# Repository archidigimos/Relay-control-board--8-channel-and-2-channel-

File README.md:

# Relay-control-board--8-channel-and-2-channel-
8 and 2 channel Relay control board. Both SMD and Throughole component version have been developed.

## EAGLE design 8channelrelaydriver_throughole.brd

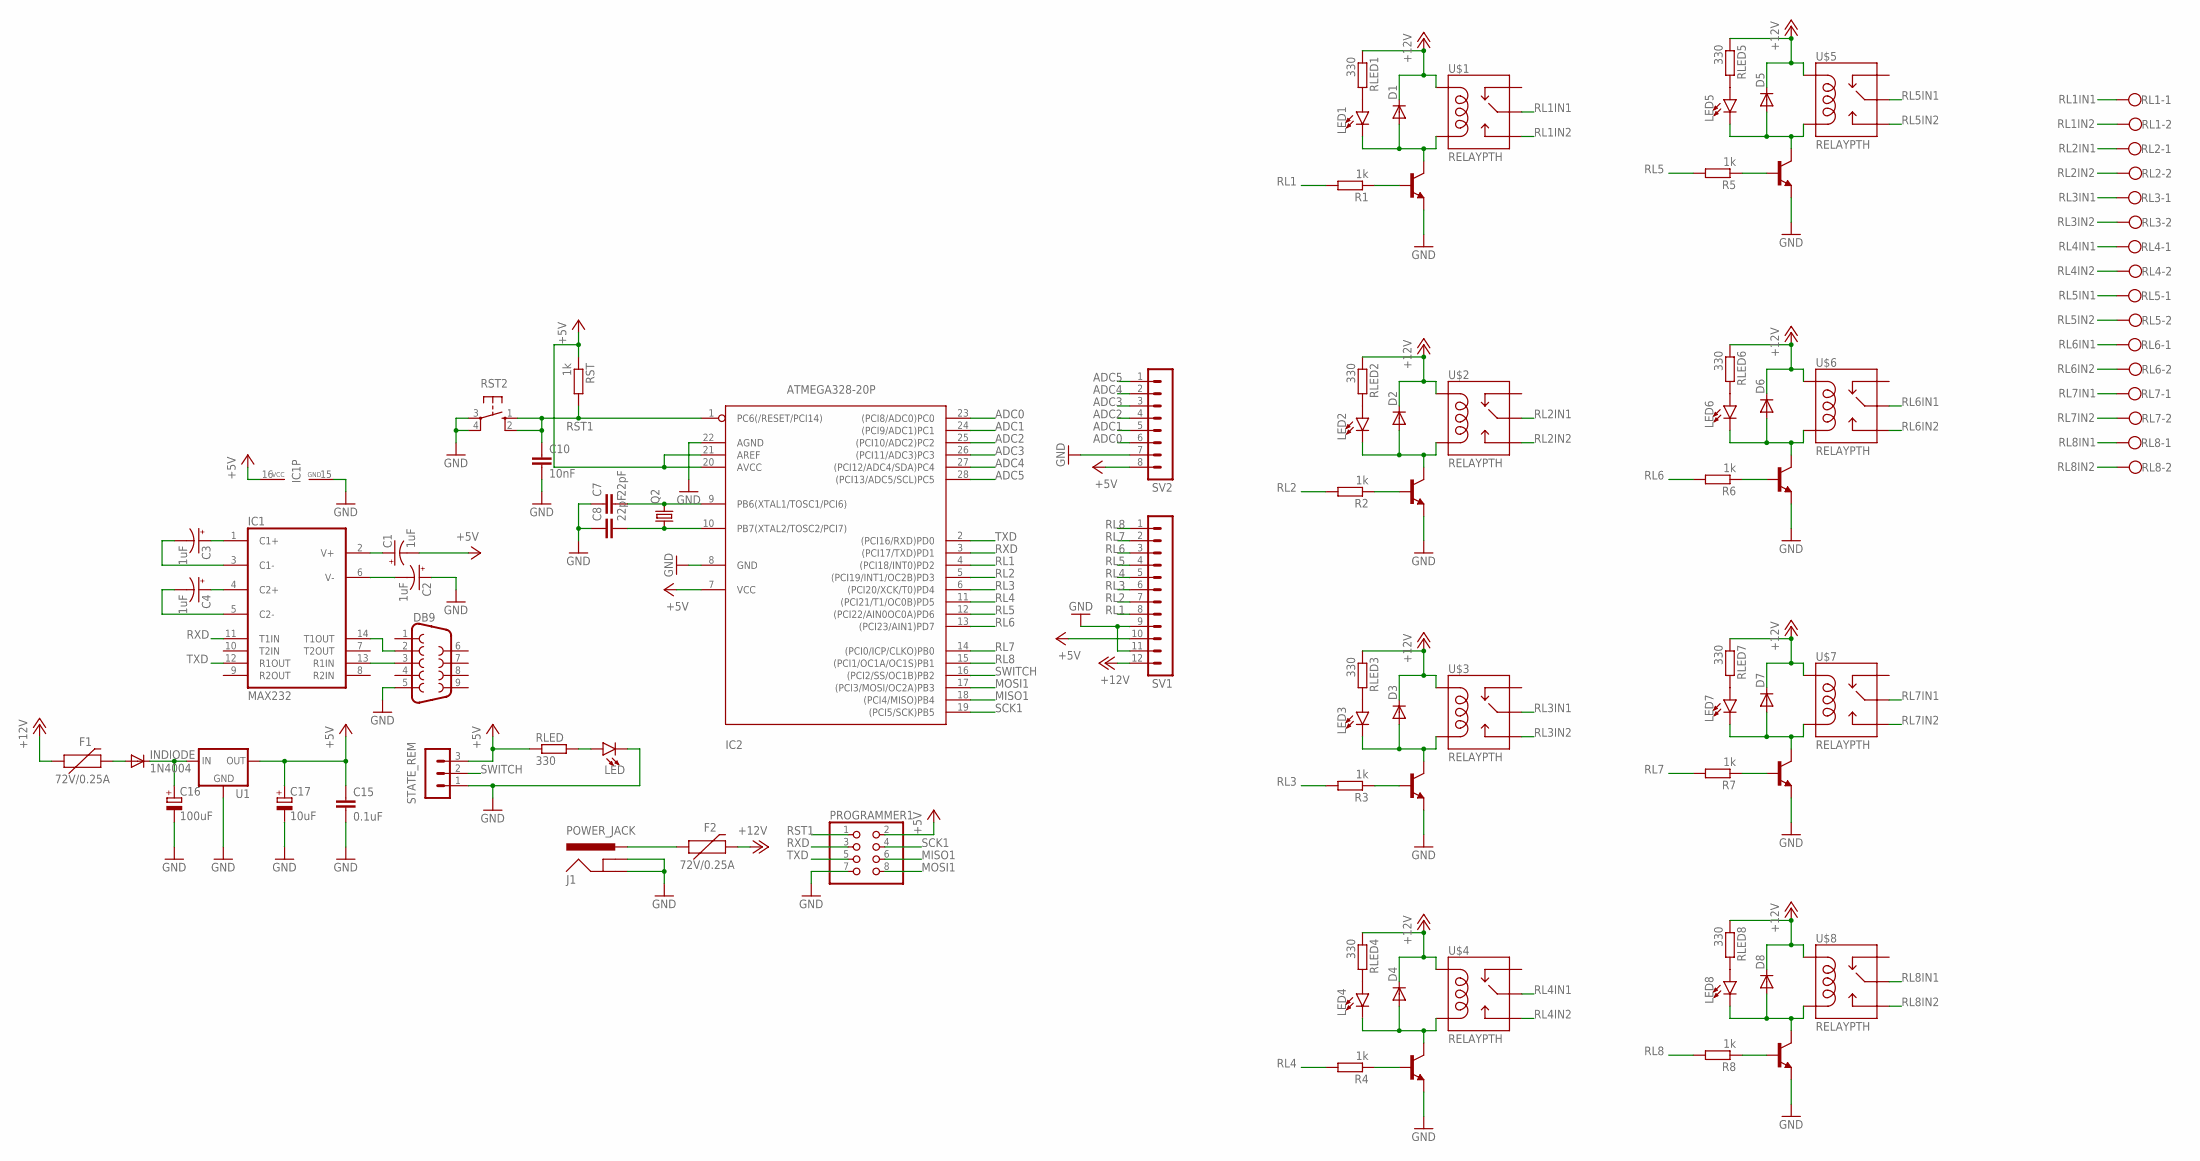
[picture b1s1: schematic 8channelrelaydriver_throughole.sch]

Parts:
C1, C2, C3, C4: 1uF; E2,5-6
C7, C8: 22pF; C025-025X050
C10: 10nF; C050-025X075
C15: 0.1uF; C050-025X075
C16: 100uF; E2,5-6
C17: 10uF; E2,5-6
D1, D2, D3, D4, D5, D6, D7, D8: 1N4004; DO41-10
DB9: DB9FEMALE; DB9
F1, F2: 72V/0.25A; PTH
IC1: MAX232; DIL16
IC2: ATMEGA328-20P; DIL28-3
INDIODE: 1N4004; DO41-10
J1: POWER_JACK; POWER_JACK_PTH
LED, LED1, LED2, LED3, LED4, LED5, LED6, LED7, LED8: LED5MM; LED_5MM
PROGRAMMER1: PINHD-2X4; 2X04
Q2: CRYSTALHC49U70; HC49U70
R1, R2, R3, R4, R5, R6, R7, R8: 1k; 0207/10
RL1, RL2, RL3, RL4, RL5, RL6, RL7, RL8: W237-102
RLED, RLED1, RLED2, RLED3, RLED4, RLED5, RLED6, RLED7, RLED8: 330; 0207/10
RST: 1k; 0207/10
RST2: 10-XX; B3F-10XX
STATE_REM: MA03-1
SV1: MA12-1
SV2: MA08-1
T1, T2, T3, T4, T5, T6, T7, T8: BC547; TO92
U1: V_REG_78XXSIDE; 78XXL
U$1, U$2, U$3, U$4, U$5, U$6, U$7, U$8: RELAYPTH; SRD-05VDC-SL-C

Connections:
+12V: D1.C, D2.C, D3.C, D4.C, D5.C, D6.C, D7.C, D8.C, F1.P$1 (1), F2.P$2 (2), RLED1.1, RLED2.1, RLED3.1, RLED4.1, RLED5.1, RLED6.1, RLED7.1, RLED8.1, SV1.12, U$1.COIL1, U$2.COIL1, U$3.COIL1, U$4.COIL1, U$5.COIL1, U$6.COIL1, U$7.COIL1, U$8.COIL1
ADC0: IC2.23 ((PCI8/ADC0)PC0), SV2.6
ADC1: IC2.24 ((PCI9/ADC1)PC1), SV2.5
ADC2: IC2.25 ((PCI10/ADC2)PC2), SV2.4
ADC3: IC2.26 ((PCI11/ADC3)PC3), SV2.3
ADC4: IC2.27 ((PCI12/ADC4/SDA)PC4), SV2.2
ADC5: IC2.28 ((PCI13/ADC5/SCL)PC5), SV2.1
MISO1: IC2.18 ((PCI4/MISO)PB4), PROGRAMMER1.6
MOSI1: IC2.17 ((PCI3/MOSI/OC2A)PB3), PROGRAMMER1.8
unnamed: DB9.2, IC1.14 (T1OUT)
unnamed: LED.A, RLED.2
unnamed: C16.+, INDIODE.C, U1.IN
unnamed: D2.A, LED2.K (C), T2.3 (C), U$2.COIL0
unnamed: D1.A, LED1.K (C), T1.3 (C), U$1.COIL0
unnamed: R1.1, T1.2 (B)
unnamed: R2.1, T2.2 (B)
unnamed: D3.A, LED3.K (C), T3.3 (C), U$3.COIL0
unnamed: R3.1, T3.2 (B)
unnamed: D4.A, LED4.K (C), T4.3 (C), U$4.COIL0
unnamed: R4.1, T4.2 (B)
unnamed: D5.A, LED5.K (C), T5.3 (C), U$5.COIL0
unnamed: R5.1, T5.2 (B)
unnamed: D6.A, LED6.K (C), T6.3 (C), U$6.COIL0
unnamed: R6.1, T6.2 (B)
unnamed: D7.A, LED7.K (C), T7.3 (C), U$7.COIL0
unnamed: R7.1, T7.2 (B)
unnamed: C1.+, IC1.2 (V+)
unnamed: D8.A, LED8.K (C), T8.3 (C), U$8.COIL0
unnamed: C2.-, IC1.6 (V-)
unnamed: C7.2, IC2.9 (PB6(XTAL1/TOSC1/PCI6)), Q2.2
unnamed: C8.2, IC2.10 (PB7(XTAL2/TOSC2/PCI7)), Q2.1
unnamed: C3.+, IC1.1 (C1+)
unnamed: C4.+, IC1.4 (C2+)
unnamed: C4.-, IC1.5 (C2-)
unnamed: C3.-, IC1.3 (C1-)
unnamed: R8.1, T8.2 (B)
unnamed: F1.P$2 (2), INDIODE.A
unnamed: LED1.A, RLED1.2
unnamed: F2.P$1 (1), J1.PWR
unnamed: LED2.A, RLED2.2
unnamed: LED3.A, RLED3.2
unnamed: LED4.A, RLED4.2
unnamed: LED5.A, RLED5.2
unnamed: LED6.A, RLED6.2
unnamed: LED7.A, RLED7.2
unnamed: LED8.A, RLED8.2
PIN13: DB9.3, IC1.13 (R1IN)
RL1: IC2.4 ((PCI18/INT0)PD2), R1.2, SV1.8
RL1IN1: RL1.1, U$1.SWCOMMON
RL1IN2: RL1.2, U$1.SWOPEN
RL2: IC2.5 ((PCI19/INT1/OC2B)PD3), R2.2, SV1.7
RL2IN1: RL2.1, U$2.SWCOMMON
RL2IN2: RL2.2, U$2.SWOPEN
RL3: IC2.6 ((PCI20/XCK/T0)PD4), R3.2, SV1.6
RL3IN1: RL3.1, U$3.SWCOMMON
RL3IN2: RL3.2, U$3.SWOPEN
RL4: IC2.11 ((PCI21/T1/OC0B)PD5), R4.2, SV1.5
RL4IN1: RL4.1, U$4.SWCOMMON
RL4IN2: RL4.2, U$4.SWOPEN
RL5: IC2.12 ((PCI22/AIN0OC0A)PD6), R5.2, SV1.4
RL5IN1: RL5.1, U$5.SWCOMMON
RL5IN2: RL5.2, U$5.SWOPEN
RL6: IC2.13 ((PCI23/AIN1)PD7), R6.2, SV1.3
RL6IN1: RL6.1, U$6.SWCOMMON
RL6IN2: RL6.2, U$6.SWOPEN
RL7: IC2.14 ((PCI0/ICP/CLKO)PB0), R7.2, SV1.2
RL7IN1: RL7.1, U$7.SWCOMMON
RL7IN2: RL7.2, U$7.SWOPEN
RL8: IC2.15 ((PCI1/OC1A/OC1S)PB1), R8.2, SV1.1
RL8IN1: RL8.1, U$8.SWCOMMON
RL8IN2: RL8.2, U$8.SWOPEN
RST1: C10.1, IC2.1 (PC6(/RESET/PCI14)), PROGRAMMER1.1, RST.2, RST2.1 (S), RST2.2 (S1)
RXD: IC1.11 (T1IN), IC2.3 ((PCI17/TXD)PD1), PROGRAMMER1.3
SCK1: IC2.19 ((PCI5/SCK)PB5), PROGRAMMER1.4
SWITCH: IC2.16 ((PCI2/SS/OC1B)PB2), STATE_REM.2
TXD: IC1.12 (R1OUT), IC2.2 ((PCI16/RXD)PD0), PROGRAMMER1.5
VDD: C1.-, C15.1, C17.+, IC1.16 (VCC), IC2.7 (VCC), IC2.20 (AVCC), IC2.21 (AREF), PROGRAMMER1.2, RLED.1, RST.1, STATE_REM.3, SV1.10, SV2.8, U1.OUT
VSS: C2.+, C7.1, C8.1, C10.2, C15.2, C16.-, C17.-, DB9.5, IC1.15 (GND), IC2.8 (GND), IC2.22 (AGND), J1.GND, J1.GNDBREAK, LED.K (C), PROGRAMMER1.7, RST2.3, RST2.4 (P1), STATE_REM.1, SV1.9, SV1.11, SV2.7, T1.1 (E), T2.1 (E), T3.1 (E), T4.1 (E), T5.1 (E), T6.1 (E), T7.1 (E), T8.1 (E), U1.GND

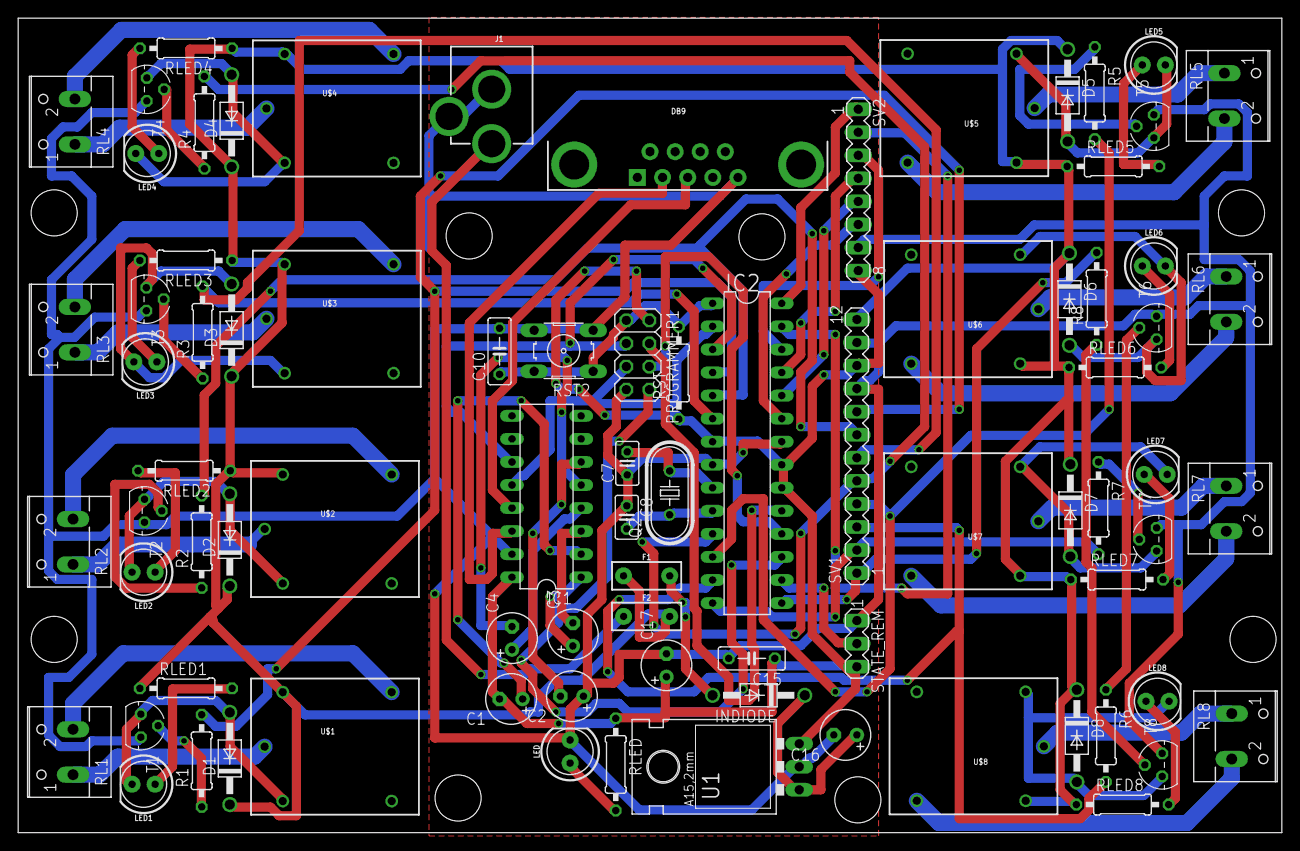
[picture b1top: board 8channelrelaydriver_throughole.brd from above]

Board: 2 copper layers, 139.2 x 89.7 mm, 83 parts (0 on the bottom side), 78 nets.

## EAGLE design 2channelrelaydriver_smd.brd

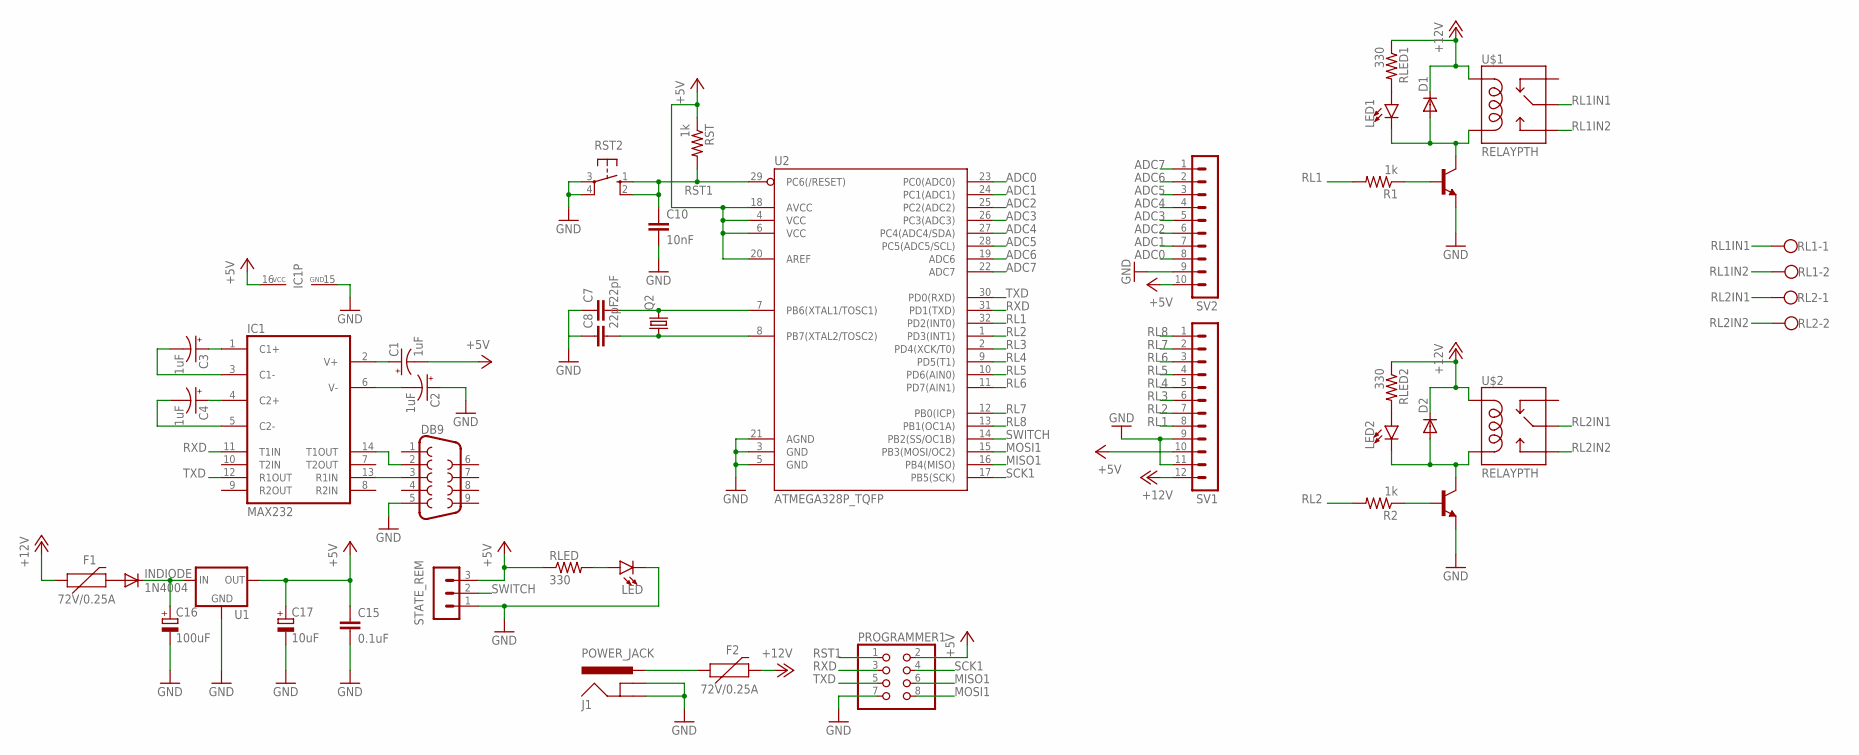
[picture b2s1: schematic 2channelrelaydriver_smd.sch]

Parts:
C1, C2, C3, C4: 1uF; E2,5-6
C7, C8: 22pF; C1206
C10: 10nF; C1206
C15: 0.1uF; C1206
C16: 100uF; E2,5-6
C17: 10uF; E2,5-6
D1, D2: 1N4004; DO41-10
DB9: DB9FEMALE; DB9
F1, F2: 72V/0.25A; PTH
IC1: MAX232; DIL16
INDIODE: 1N4004; DO41-10
J1: POWER_JACK; POWER_JACK_PTH
LED, LED1, LED2: LED5MM; LED_5MM
PROGRAMMER1: PINHD-2X4; 2X04
Q2: CRYSTALHC49U70; HC49U70
R1, R2: 1k; M1206
RL1, RL2: W237-102
RLED, RLED1, RLED2: 330; M1206
RST: 1k; M1206
RST2: 10-XX; B3F-10XX
STATE_REM: MA03-1
SV1: MA12-1
SV2: MA10-1
T1, T2: BC847; SOT23
U1: V_REG_78XXSIDE; 78XXL
U2: ATMEGA328P_TQFP; TQFP32-08
U$1, U$2: RELAYPTH; SRD-05VDC-SL-C

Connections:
+12V: D1.C, D2.C, F1.P$1 (1), F2.P$2 (2), RLED1.1, RLED2.1, SV1.12, U$1.COIL1, U$2.COIL1
ADC0: SV2.8, U2.23 (PC0(ADC0))
ADC1: SV2.7, U2.24 (PC1(ADC1))
ADC2: SV2.6, U2.25 (PC2(ADC2))
ADC3: SV2.5, U2.26 (PC3(ADC3))
ADC4: SV2.4, U2.27 (PC4(ADC4/SDA))
ADC5: SV2.3, U2.28 (PC5(ADC5/SCL))
ADC6: SV2.2, U2.19 (ADC6)
ADC7: SV2.1, U2.22 (ADC7)
MISO1: PROGRAMMER1.6, U2.16 (PB4(MISO))
MOSI1: PROGRAMMER1.8, U2.15 (PB3(MOSI/OC2))
unnamed: DB9.2, IC1.14 (T1OUT)
unnamed: LED.A, RLED.2
unnamed: C16.+, INDIODE.C, U1.IN
unnamed: D2.A, LED2.K (C), T2.3 (C), U$2.COIL0
unnamed: D1.A, LED1.K (C), T1.3 (C), U$1.COIL0
unnamed: R1.1, T1.1 (B)
unnamed: R2.1, T2.1 (B)
unnamed: LED1.A, RLED1.2
unnamed: LED2.A, RLED2.2
unnamed: F2.P$1 (1), J1.PWR
unnamed: C1.+, IC1.2 (V+)
unnamed: C2.-, IC1.6 (V-)
unnamed: C7.2, Q2.2, U2.7 (PB6(XTAL1/TOSC1))
unnamed: C8.2, Q2.1, U2.8 (PB7(XTAL2/TOSC2))
unnamed: C3.+, IC1.1 (C1+)
unnamed: C4.+, IC1.4 (C2+)
unnamed: C4.-, IC1.5 (C2-)
unnamed: C3.-, IC1.3 (C1-)
unnamed: F1.P$2 (2), INDIODE.A
PIN13: DB9.3, IC1.13 (R1IN)
RL1: R1.2, SV1.8, U2.32 (PD2(INT0))
RL1IN1: RL1.1, U$1.SWCOMMON
RL1IN2: RL1.2, U$1.SWOPEN
RL2: R2.2, SV1.7, U2.1 (PD3(INT1))
RL2IN1: RL2.1, U$2.SWCOMMON
RL2IN2: RL2.2, U$2.SWOPEN
RL3: SV1.6, U2.2 (PD4(XCK/T0))
RL4: SV1.5, U2.9 (PD5(T1))
RL5: SV1.4, U2.10 (PD6(AIN0))
RL6: SV1.3, U2.11 (PD7(AIN1))
RL7: SV1.2, U2.12 (PB0(ICP))
RL8: SV1.1, U2.13 (PB1(OC1A))
RST1: C10.1, PROGRAMMER1.1, RST.2, RST2.1 (S), RST2.2 (S1), U2.29 (PC6(/RESET))
RXD: IC1.11 (T1IN), PROGRAMMER1.3, U2.31 (PD1(TXD))
SCK1: PROGRAMMER1.4, U2.17 (PB5(SCK))
SWITCH: STATE_REM.2, U2.14 (PB2(SS/OC1B))
TXD: IC1.12 (R1OUT), PROGRAMMER1.5, U2.30 (PD0(RXD))
VDD: C1.-, C15.1, C17.+, IC1.16 (VCC), PROGRAMMER1.2, RLED.1, RST.1, STATE_REM.3, SV1.10, SV2.10, U1.OUT, U2.4 (VCC), U2.6 (VCC), U2.18 (AVCC), U2.20 (AREF)
VSS: C2.+, C7.1, C8.1, C10.2, C15.2, C16.-, C17.-, DB9.5, IC1.15 (GND), J1.GND, J1.GNDBREAK, LED.K (C), PROGRAMMER1.7, RST2.3, RST2.4 (P1), STATE_REM.1, SV1.9, SV1.11, SV2.9, T1.2 (E), T2.2 (E), U1.GND, U2.3 (GND), U2.5 (GND), U2.21 (AGND)

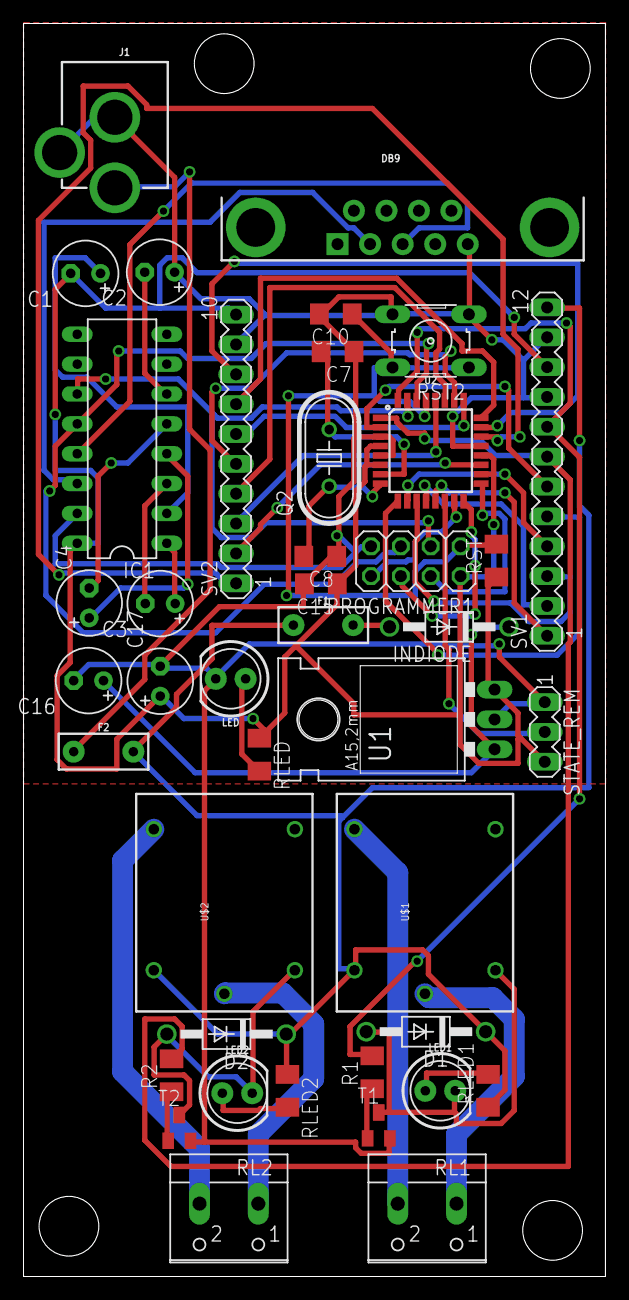
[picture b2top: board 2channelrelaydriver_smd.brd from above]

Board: 2 copper layers, 49.5 x 106.6 mm, 41 parts (0 on the bottom side), 50 nets.

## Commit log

2017-08-08 :tada: Added .gitattributes & .gitignore files
2017-08-08 Screenshot

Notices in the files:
parts and their libraries:
SparkFun-Connectors: Licensing: Creative Commons ShareAlike 4.0 International - https://creativecommons.org/licenses/by-sa/4.0
